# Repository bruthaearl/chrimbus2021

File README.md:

## chrimbus2021
PCB Christmas ornaments for 2021.

Read more about them here: https://www.oakst.io/projects/xmas-2021/

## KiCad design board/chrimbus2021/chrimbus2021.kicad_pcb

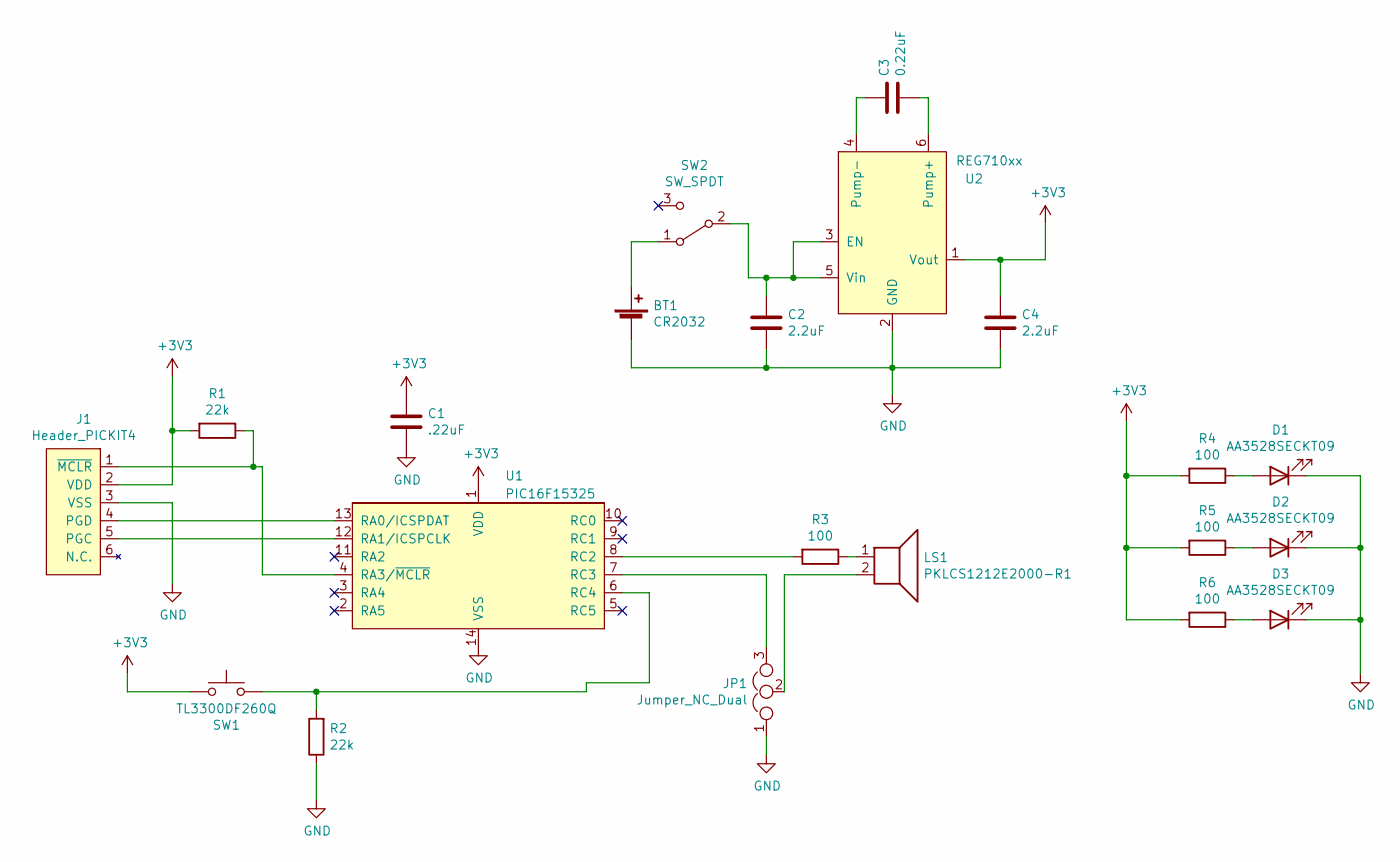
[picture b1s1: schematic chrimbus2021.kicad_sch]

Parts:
BT1: CR2032; BatteryHolder_MPD_BC2003_1x2032
C1: .22uF; C_1206_3216Metric_Pad1.33x1.80mm_HandSolder
C2, C4: 2.2uF; C_1206_3216Metric_Pad1.33x1.80mm_HandSolder
C3: 0.22uF; C_1206_3216Metric_Pad1.33x1.80mm_HandSolder
D1, D2, D3: AA3528SECKT09‎; Kingbright_AA3528
J1: Header_PICKIT4; Tag-Connect_TC2030-IDC-NL_2x03_P1.27mm_Vertical
JP1: Jumper_NC_Dual; SolderJumper-3_P1.3mm_Open_RoundedPad1.0x1.5mm
LS1: ‎PKLCS1212E2000-R1‎; PKLCS1212E2000-R1
R1, R2: 22k; R_1206_3216Metric_Pad1.30x1.75mm_HandSolder
R3, R4, R5, R6: 100; R_1206_3216Metric_Pad1.30x1.75mm_HandSolder
SW1: TL3300DF260Q‎; E_Switch_TL3300DF260Q
SW2: SW_SPDT; SW_JS102011JAQN
U1: PIC16F15325; SO-14_3.9x8.65mm_P1.27mm
U2: REG710xx; SOT-23-6_Handsoldering

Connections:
+3V3: C1.2, C4.1, J1.2 (VDD), R1.2, R4.2, R5.2, R6.2, SW1.1, U1.1 (VDD), U2.1 (Vout)
GND: BT1.2 (-), C1.1, C2.2, C4.2, D1.1 (K), D2.1 (K), D3.1 (K), J1.3 (VSS), JP1.1, R2.1, U1.14 (VSS), U2.2 (GND)
unnamed: BT1.1 (+), SW2.1 (A)
unnamed: C2.1, SW2.2 (B), U2.3 (EN), U2.5 (Vin)
unnamed: C3.1, U2.4 (Pump-)
unnamed: C3.2, U2.6 (Pump+)
unnamed: D1.2 (A), R4.1
unnamed: D2.2 (A), R5.1
unnamed: D3.2 (A), R6.1
unnamed: J1.1 (~MCLR), R1.1, U1.4 (RA3/~MCLR)
unnamed: J1.4 (PGD), U1.13 (RA0/ICSPDAT)
unnamed: J1.5 (PGC), U1.12 (RA1/ICSPCLK)
unnamed: JP1.2, LS1.2
unnamed: JP1.3, U1.7 (RC3)
unnamed: LS1.1, R3.1
unnamed: R2.2, SW1.2, U1.6 (RC4)
unnamed: R3.2, U1.8 (RC2)

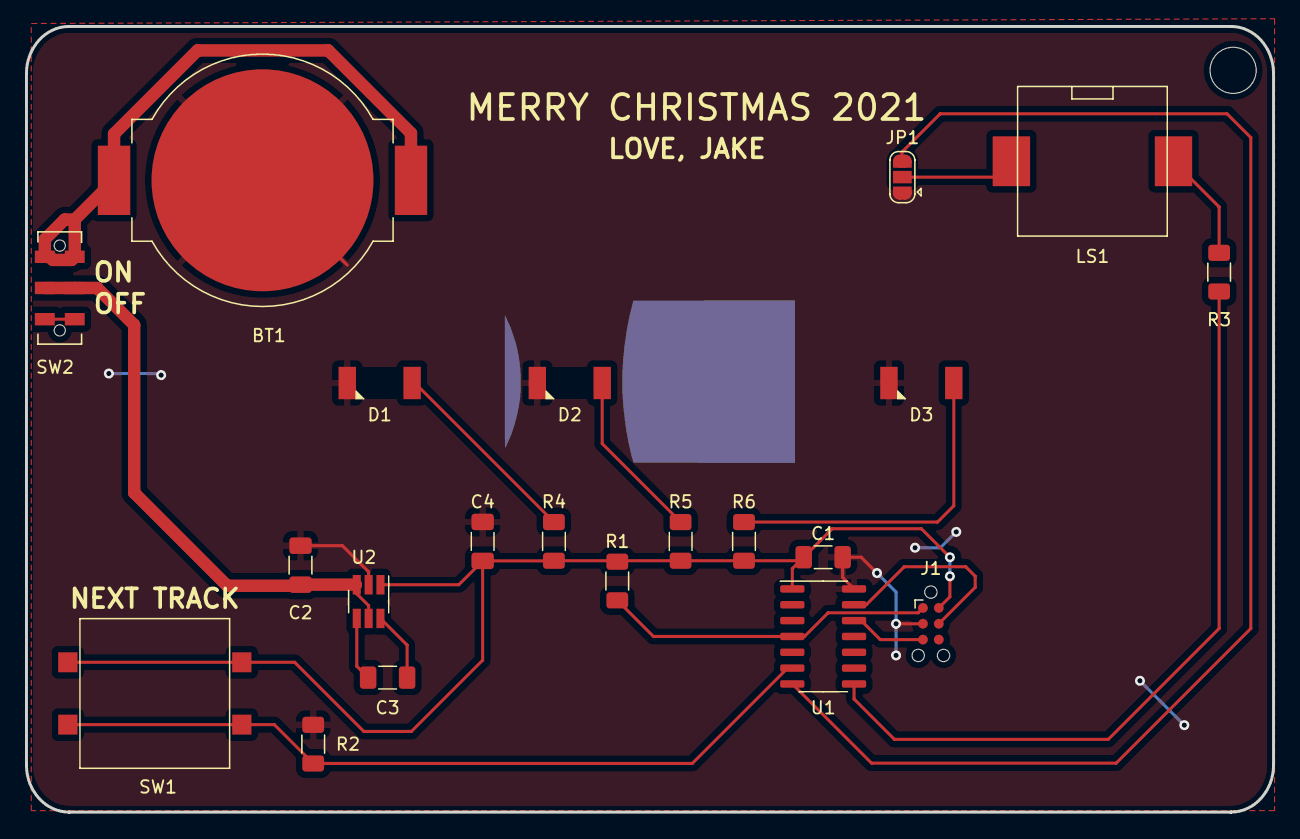
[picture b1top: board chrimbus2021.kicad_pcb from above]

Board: 2 copper layers, 100.0 x 63.0 mm, 21 parts (0 on the bottom side), 17 nets.

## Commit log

2021-12-29 readme update
